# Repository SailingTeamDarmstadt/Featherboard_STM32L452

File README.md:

# Featherboard_STM32L452
Our custom designed PCB for the STM32L452 in the Feather format design

# Warning
We added a charging circuit for a LiPo, but didn't test it previous to release. **If you want to use the charging circuit please check the design for yourself and make sure nothing bad can happen. You have been warned!**

## Intended use

We designed this board as a coprocessor for Marlin to control the onboard servo motors but also with a future use as an autopilot for roBOOTer. 

To keep the production cost low we chose the same STM microcontroller used throught our boats already.

## Feature list
- STM32L452RET chip
- USB-C connector for power supply and programming connection
- Additional programming header, simmilar to the one used throught our PCBs (usually not populated)
- DFU/programming jumper, to choose the chip mode
- Micro SD card slot to store/read data
- Status LEDs for power, charging, CAN and Timer usage as well as additional, free programable ones
- Access to CAN interface

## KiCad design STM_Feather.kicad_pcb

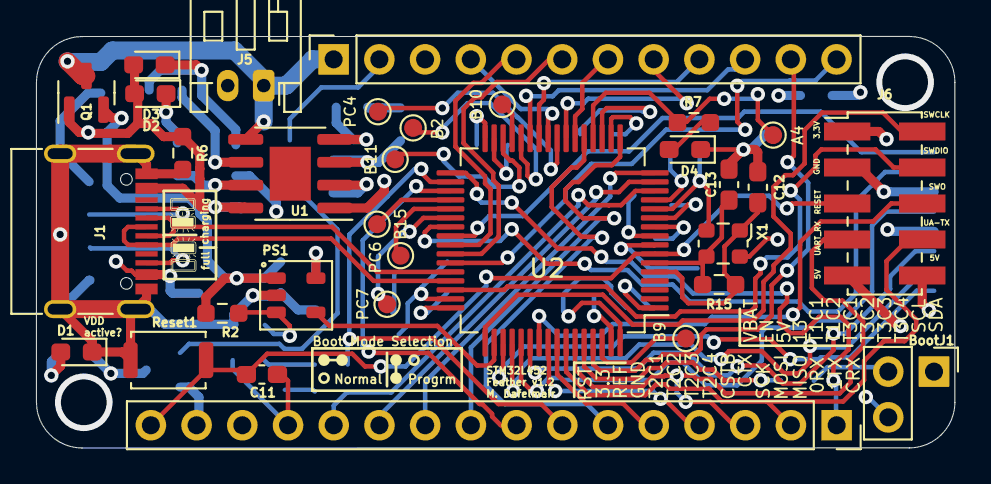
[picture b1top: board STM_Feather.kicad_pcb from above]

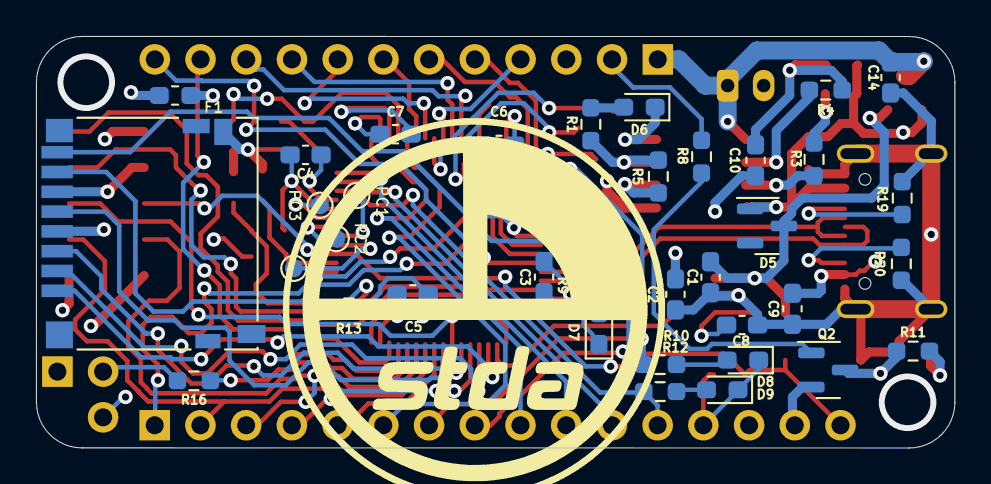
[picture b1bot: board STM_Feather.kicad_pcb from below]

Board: 4 copper layers, 51.0 x 22.9 mm, 68 parts (36 on the bottom side), 75 nets.

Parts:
A4: TestPoint; TestPoint_Pad_D1.0mm
B2, B9, B10, B11, B15: TestPoint; TestPoint_Pad_D1.0mm
BootJ1: Jumper_3_Bridged12; PinHeader_1x03_P2.54mm_90Degr
C1, C2: 1µF; C_0603_1608Metric_Pad1.08x0.95mm_HandSolder
C3: 4.7µF; C_0603_1608Metric_Pad1.08x0.95mm_HandSolder
C4, C5, C6, C7, C8, C11: 100nF; C_0603_1608Metric_Pad1.08x0.95mm_HandSolder
C9, C10, C14: 10µF; C_0603_1608Metric_Pad1.08x0.95mm_HandSolder
C12, C13: 37pF; C_0603_1608Metric_Pad1.08x0.95mm_HandSolder
D1, D2, D3, D4, D7, D8, D9: LED; LED_0603_1608Metric_Pad1.05x0.95mm_HandSolder
D5: ZHCS1000; SOT-23
D6: D_Zener; D_0603_1608Metric_Pad1.05x0.95mm_HandSolder
F1: Fuse_Small; Fuse_0603_1608Metric_Pad1.05x0.95mm_HandSolder
J1: USB_C_Receptacle_USB2.0; USB_C_Receptacle_G-Switch_GT-USB-7010ASV
J2: Conn_01x12_Female; PinSocket_1x12_P2.54mm_Vertical
J3: Conn_01x16_Female; PinSocket_1x16_P2.54mm_Vertical
J4: Micro_SD_Card; microSD_HC_Hirose_DM3D-SF
J5: Conn_01x02; JST_PH_S2B-PH-K_1x02_P2.00mm_Horizontal
J6: Conn_02x05_Odd_Even; PinHeader_2x05_P2.00mm_Vertical_SMD
PC0, PC1, PC2, PC3, PC4, PC6, PC7: TestPoint; TestPoint_Pad_D1.0mm
PS1: MCP1754T-3302E_OT; SOT-23-5
Q1, Q2: DMG1045U; SOT-23
R1: 50k; R_0603_1608Metric_Pad0.98x0.95mm_HandSolder
R2: 47k; R_0603_1608Metric_Pad0.98x0.95mm_HandSolder
R3, R4, R7, R9, R10, R11, R12: 1k; R_0603_1608Metric_Pad0.98x0.95mm_HandSolder
R5: 5k; R_0603_1608Metric_Pad0.98x0.95mm_HandSolder
R6: 100k; R_0603_1608Metric_Pad0.98x0.95mm_HandSolder
R8, R16: 10k; R_0603_1608Metric_Pad0.98x0.95mm_HandSolder
R13: 0; R_0603_1608Metric_Pad0.98x0.95mm_HandSolder
R15: 1M; R_0603_1608Metric_Pad0.98x0.95mm_HandSolder
R19, R20: 5,1k; R_0603_1608Metric_Pad0.98x0.95mm_HandSolder
Reset1: SW_Push; SW_Push_SPST_NO_Alps_SKRK
U1: TP4056; SOIC-8-1EP_3.9x4.9mm_P1.27mm_EP2.29x3mm
U2: STM32L452RETx; LQFP-64_10x10mm_P0.5mm
X1: ECS-2520MV-xxx-xx; Oscillator_SMD_ECS_2520MV-xxx-xx-4Pin_2.5x2.0mm

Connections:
3Vsup: J3.15, Q2.2 (S)
+BATT: C14.2, J2.1, J5.1, Q1.3 (D), U1.5 (BAT)
/0 RX: J3.3, J6.7, U2.59 (PB7)
/1 TX: J3.2, J6.8, U2.58 (PB6)
/5: J2.10, U2.27 (PB1)
/6: J2.9, U2.26 (PB0)
/9: J2.8, U2.23 (PA7)
/10: J2.7, U2.22 (PA6)
/11: J2.6, U2.42 (PA9)
/12: J2.5, U2.41 (PA8)
/A0: J3.12, R12.1, U2.14 (PA0)
/A1: J3.11, U2.15 (PA1)
/A2: J3.10, U2.16 (PA2)
/A3: J3.9, U2.17 (PA3)
/A4: J3.8, U2.35 (PB14)
/A5: J3.7, R10.1, U2.34 (PB13)
/CAN1_RX: J3.1, U2.33 (PB12)
/Ext_5V: F1.1, J6.9, J6.10
/I2C1_SCL: J2.11, U2.61 (PB8)
/I2C1_SDA: J2.12, U2.43 (PA10)
/MISO: J3.4, U2.56 (PB4)
/MOSI: J3.5, U2.57 (PB5)
/SCK: J3.6, U2.21 (PA5)
/SDMMC1_CK: J4.5 (CLK), U2.53 (PC12)
/SDMMC1_CMD: J4.3 (CMD), U2.54 (PD2)
/SDMMC1_D0: J4.7 (DAT0), U2.39 (PC8)
/SDMMC1_D1: J4.8 (DAT1), U2.40 (PC9)
/SDMMC1_D2: J4.1 (DAT2), U2.51 (PC10)
/SDMMC1_D3: J4.2 (DAT3/CD), U2.52 (PC11)
/SYS_JMTS-SWDIO: J6.4, U2.46 (PA13)
/SYS_JTCK-SWCLK: J6.2, U2.49 (PA14)
/SYS_JTDI: B15.1, U2.36 (PB15)
/SYS_JTDO-SWO: J6.6, U2.55 (PB3)
/USB_DM: J1.A7 (D-), J1.B7 (D-), U2.44 (PA11)
/USB_DP: J1.A6 (D+), J1.B6 (D+), U2.45 (PA12)
ADC-WKUP: J2.4, U2.25 (PC5)
BOOT: R16.1, U2.60 (PH3)
EN: J2.2, R8.1
GND: BootJ1.3 (B), C1.2, C2.2, C3.2, C4.2, C5.2, C6.2, C7.2, C8.2, C9.2, C10.1, C11.2, C12.1, C13.2, C14.1, D1.1 (K), D4.1 (K), D7.1 (K), D8.1 (K), D9.1 (K), J1.A1 (GND), J1.A12 (GND), J1.B1 (GND), J1.B12 (GND), J1.S1 (SHIELD), J3.13, J4.6 (VSS), J4.9 (SHIELD), J5.2, J6.3, PS1.2 (GND), R1.2, R5.1, R6.2, R19.1, R20.1, Reset1.1, U1.1 (TEMP), U1.3 (GND), U2.12 (VSSA), U2.18 (VSS), U2.31 (VSS), U2.47 (VSS), U2.63 (VSS), X1.2 (GND)
unnamed: BootJ1.2 (C), R16.2
unnamed: D1.2 (A), R11.2
unnamed: D2.1 (K), R3.1
unnamed: C10.2, D3.1 (K), R4.1
unnamed: D4.2 (A), R7.1
unnamed: D6.2 (A), R1.1
unnamed: D7.2 (A), R9.1
unnamed: D8.2 (A), R10.2
unnamed: D9.2 (A), R12.2
unnamed: J1.A5 (CC1), R19.2
unnamed: J1.B5 (CC2), R20.2
unnamed: C8.1, PS1.3 (~SHDN), R2.2
unnamed: Q2.1 (G), R8.2
unnamed: R5.2, U1.2 (PROG)
unnamed: R3.2, U1.7 (~CHRG)
unnamed: R4.2, U1.6 (~STDBY)
unnamed: A4.1, R7.2, U2.20 (PA4)
unnamed: B2.1, U2.28 (PB2)
unnamed: B9.1, U2.62 (PB9)
unnamed: B10.1, U2.29 (PB10)
unnamed: B11.1, U2.30 (PB11)
unnamed: PC0.1, U2.8 (PC0)
unnamed: PC1.1, U2.9 (PC1)
unnamed: PC2.1, U2.10 (PC2)
unnamed: PC3.1, U2.11 (PC3)
unnamed: PC4.1, U2.24 (PC4)
unnamed: PC6.1, U2.37 (PC6)
unnamed: PC7.1, R9.2, U2.38 (PC7)
unnamed: R13.1, U2.1 (VBAT)
OSC_IN: C12.2, R15.1, U2.5 (PH0), X1.1 (Tri-State)
OSC_OUT: C13.1, R15.2, U2.6 (PH1), X1.3 (OUT)
RESET: C11.1, J3.16, J6.5, Reset1.2, U2.7 (NRST)
UV_DET: PS1.4 (PWRGD), U2.50 (PA15)
VBUS: C9.1, D2.2 (A), D3.2 (A), D5.1 (A), D6.1 (K), F1.2, J1.A4 (VBUS), J1.A9 (VBUS), J1.B4 (VBUS), J1.B9 (VBUS), J2.3, Q1.1 (G), R6.1, U1.4 (VCC), U1.8 (CE)
VCC: C1.1, D5.3 (K), PS1.1 (VIN), Q1.2 (S), R2.1
VDD: BootJ1.1 (A), C2.1, C3.1, C4.1, C5.1, C6.1, C7.1, J4.4 (VDD), J6.1, PS1.5 (VOUT), Q2.3 (D), R11.1, R13.2, U2.13 (VDDA), U2.19 (VDD), U2.32 (VDD), U2.48 (VDDUSB), U2.64 (VDD), X1.4 (VDD)

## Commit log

2025-02-05 Init release commit
2025-02-05 Added warning to readme
